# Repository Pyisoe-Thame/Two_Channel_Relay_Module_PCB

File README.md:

# Two Channel Relay Module

This is the blueprint for a 2-Channel relay module that can be driven by 5V like a usual one.

What is unusual are the SMD LEDs placed instead of the THT ones.
This makes the PCB designing more challenging (not for the practical design but for the aesthetic or theoritical one).

The component is a little immature but seem to be prettier and a bit amusing.
## Demo

The project is supposed to be opened with KiCad EDA. The file with the extension .kicad_pro work the same as a main file.

In the plotted pdf file, there included the schematic diagram of the whole circuit. Even the mounting holes are not excluded.

The pictures of the PCB design and 3D view for demo purpose are provided for under the "images" folder.

## Screenshots

## License

[MIT](https://choosealicense.com/licenses/mit/)
License

Copyright (c) 2024 Pyisoe-Thame

Permission is hereby granted, free of charge, to any person obtaining a copy
of this software and associated documentation files (the "Software"), to deal
in the Software without restriction, including without limitation the rights
to use, copy, modify, merge, publish, distribute, sublicense, and/or sell
copies of the Software, and to permit persons to whom the Software is
furnished to do so, subject to the following conditions:

The above copyright notice and this permission notice shall be included in all
copies or substantial portions of the Software.

## Support

For support, email pyisoethame@gmail.com.

## Authors

- [@Pyisoe-Thame](https://github.com/Pyisoe-Thame)

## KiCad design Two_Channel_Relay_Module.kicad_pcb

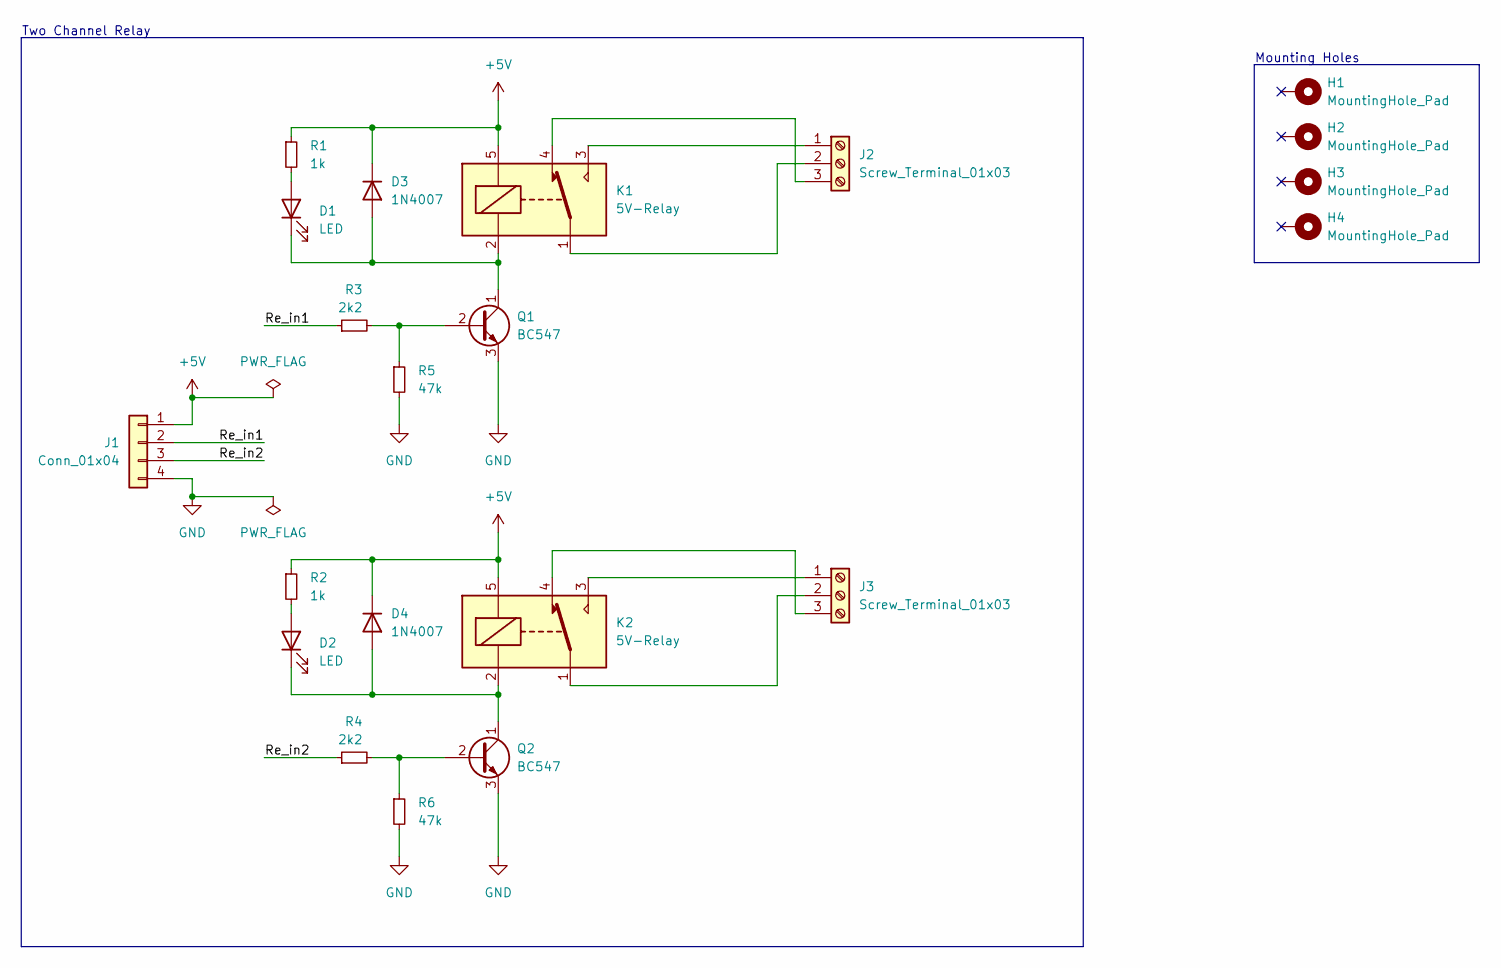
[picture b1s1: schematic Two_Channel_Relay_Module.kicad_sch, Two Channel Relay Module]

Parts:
D1, D2: LED; LED_0603_1608Metric
D3, D4: 1N4007; D_DO-41_SOD81_P10.16mm_Horizontal
H1, H2, H3, H4: MountingHole_Pad; MountingHole_3.2mm_M3_Pad
J1: Conn_01x04; PinHeader_1x04_P2.54mm_Vertical
J2, J3: Screw_Terminal_01x03; TerminalBlock_Phoenix_MKDS-1,5-3-5.08_1x03_P5.08mm_Horizont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
K1, K2: 5V-Relay; Relay_SPDT_SANYOU_SRD_Series_Form_C
Q1, Q2: BC547; TO-92S_Wide
R1, R2: 1k; R_0603_1608Metric
R3, R4: 2k2; R_0603_1608Metric
R5, R6: 47k; R_0603_1608Metric

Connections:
+5V: D3.1 (K), D4.1 (K), J1.1, K1.5, K2.5, R1.1, R2.1
/Re_in1: J1.2, R3.1
/Re_in2: J1.3, R4.1
GND: J1.4, Q1.3 (E), Q2.3 (E), R5.2, R6.2
unnamed: D1.2 (A), R1.2
unnamed: D1.1 (K), D3.2 (A), K1.2, Q1.1 (C)
unnamed: D2.2 (A), R2.2
unnamed: D2.1 (K), D4.2 (A), K2.2, Q2.1 (C)
unnamed: J2.1, K1.3
unnamed: J2.2, K1.1
unnamed: J2.3, K1.4
unnamed: J3.1, K2.3
unnamed: J3.2, K2.1
unnamed: J3.3, K2.4
unnamed: Q1.2 (B), R3.2, R5.1
unnamed: Q2.2 (B), R4.2, R6.1

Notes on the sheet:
Mounting Holes
Two Channel Relay

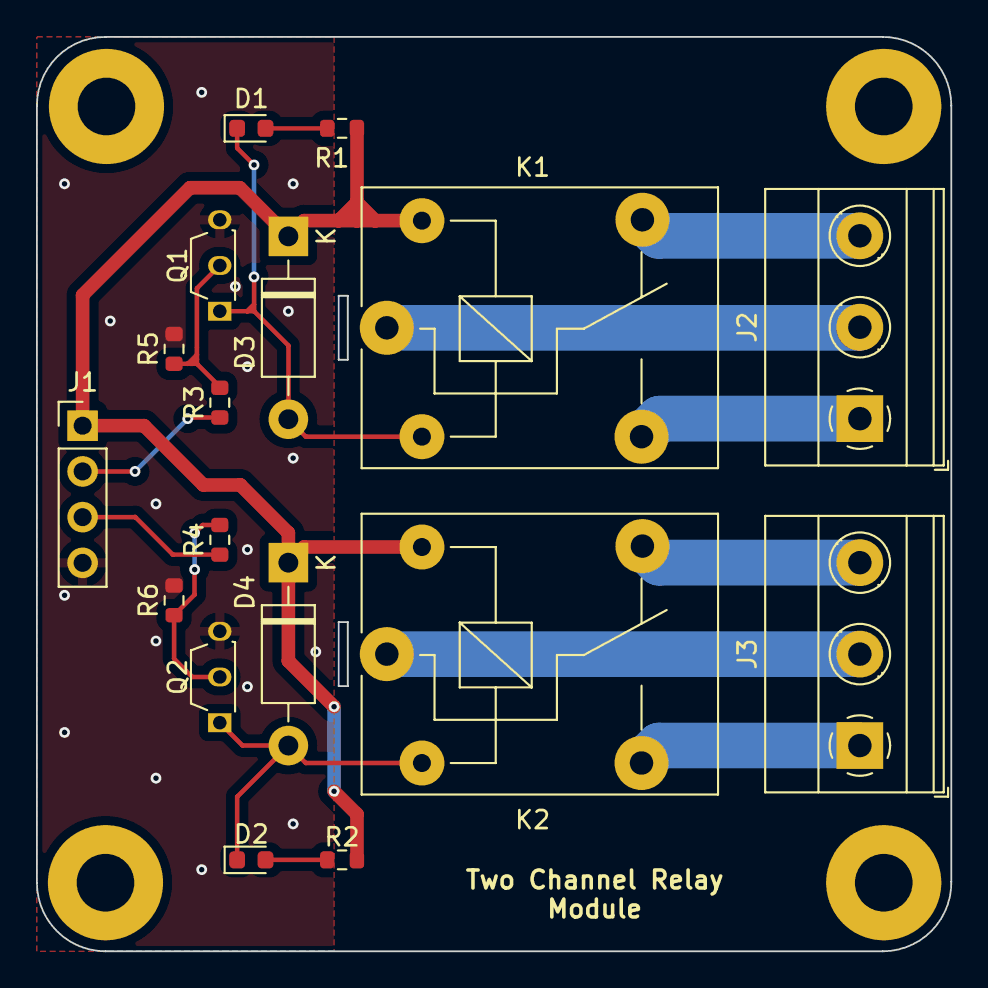
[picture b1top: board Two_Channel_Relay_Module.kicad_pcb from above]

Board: 2 copper layers, 50.8 x 50.8 mm, 21 parts (0 on the bottom side), 16 nets.

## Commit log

2024-01-22 commit_1
